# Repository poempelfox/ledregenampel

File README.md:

# LED-Regen-Ampel

## Intro

This is a small project that contains hardware design and
firmware for a small traffic-light-style display that shows
whether you can leave the house without getting wet. As it
utilizes regenampel.de to get the prediction, this is pretty
much useless outside of germany, which is why the rest of
the description is in german.

Haupt-Ziel dieses Projekts war es, mal eine Platine mit
richtig vielen LEDs drauf zu designen, um sie dann von einem
guenstigen Chinesischen Prototypenfertiger (JLCPCB) anfertigen
zu lassen.
Da ich ein Fan der [Regenampel](https://regenampel.de)
bin, kam die Idee auf, eine aus ganz vielen LEDs bestehende
Regenampel zu konstruieren, in einer Groesse die man bequem
neben die Wohnungstuer oder auch die Tuer des [ZAM](https://zam.haus)
haengen kann.

## Hardware Beschreibung Grob-Uebersicht

* ca. 21 x 7,5 cm grosse Platine
* Rot / Gelb / Gruen bestehend aus je 51 in konzentrischen Kreisen
  angeordneten LEDs (keine superhellen, generische in 0805 Gehaeuse),
  Durchmesser 5 cm.
* kleines OLED-Display unter der Ampel, um den Zusatztext den die
  Regenampel in manchen Situationen liefert (Beispiel: "Noch 20 Minuten
  starker Niederschlag") anzeigen zu koennen.
* Ein WaveShare ESP32-C3-Zero dient als zentrale Steuerung. Er wird
  auf die Rueckseite geloetet.
* Der ESP32-C3 steuert die LEDs ueber je einen MOSFET pro Farbe
  mit einem dedizierten I/O-Pin pro Farbe. Die Helligkeit kann dabei
  fuer jede Farbe einzeln ueber PWM mit 4096 Stufen geregelt werden.
  Das OLED wird ueber I2C angesprochen.
* momentaner Status: Hardware wurde geliefert und funktioniert zumindest
  teilweise.

## Hardware-Beschreibung Detail

Die Platine wurde in KiCad entworfen.
Die KiCad-Dateien finden sich im Unterverzeichnis [kicad/](kicad/).

Um die Platine nachbauen zu lassen, braucht man moeglicherweise
nichtmal KiCad zu oeffnen: Denn im Unterverzeichnis
[kicad/ledregenampel/jlcpcb/production_files/](kicad/ledregenampel/jlcpcb/production_files/)
finden sich die drei Dateien, die JLCPCB benoetigt um die Platine
zu fertigen: Das gerber-.zip, die BOM (Bill Of Materials), und das
CPL (Component PLacement). Verwendet wurde das, was im Juli 2024
dort auf Lager war. Solltet ihr zu einem spaeteren Zeitpunkt versuchen
das auch fertigen zu lassen, koennte es natuerlich sein dass Teile
nicht auf Lager sind und ersetzt werden muessen. Anders formuliert: YMMV.

Neben der gefertigten Platine sind nur zwei zusaetzliche Teile
notwendig:

* WaveShare ESP32-C3-Zero. Ein Microcontroller mit castellated mounting
  holes, so dass man ihn ohne Gefummel mit Buchsen- und Stiftleisten
  einfach auf die Rueckseite der Platine loeten kann. Der C3 ist zum
  Zeitpunkt dieses Projekts einer der kleinsten (und billigsten)
  Microcontroller die Espressif anbietet, fuer die ihm hier zugedachten
  Aufgaben aber immer noch deutlich ueberdimensioniert. Auf der
  Waveshare-Platine befindet sich u.a. eine USB-C-Buchse und ein
  Spannungsregler (Linearregler :-/) fuer die 3.3V.
* [Ein von TinyTronics bezogenes 2.08 inch OLED-Display mit 256x64 Pixeln](https://www.tinytronics.nl/en/displays/oled/2.08-inch-oled-display-256*64-pixels-white-i2c). Ich hatte
  ernsthafte Probleme, ein meinen Anforderungen nach "nicht winzig, I2C,
  extra-wide, 3.3V" entsprechendes Display zu finden, das war eines der
  wenigen passenden Angebote. Es handelt sich um ein Display
  des zumindest mir voellig unbekannten Herstellers "ZHONGJINGYUAN"
  mit einem SHT1122 Controller. Das Display wird ueber I2C
  angesprochen. Es wird auf die Vorderseite der LED-Regenampel-
  Platine geloetet.

Die USB-C-Buchse auf dem ESP32-Board ist der normale Weg, um
das Projekt mit Strom zu versorgen. USB-Power und "5V" Schiene
auf der Platine sind dabei einfach durchverbunden, d.h. es darf
falls auf andere Weise 5V eingespeist werden KEINESFALLS
gleichzeitig USB-C verbunden werden. Es ist ausserdem zu
beachten, dass der erwartete Stromverbrauch einer einzigen
Ampelfarbe bei 100% Helligkeit um 1A liegt. Es empfiehlt sich
also nicht, mehrere Ampelfarben gleichzeitig mit hoher
Helligkeit leuchten zu lassen.

Uebrigens sind 100% Helligkeit generell nicht der intendierte
Betriebsmodus. Mal abgesehen von dem geringfuegigen Problem,
dass das vermutlich den Betrachter der Ampel blind machen
wuerde, ist auch die dabei entstehende Abwaerme enorm -
die Platine wuerde wahrscheinlich recht schnell ueberhitzen.
"Normal" ist PWM mit unter 20% duty cycle...

## Hardware - known bugs

* Der ESP32-C3 wurde bei ersten Vorabtests alleine unangenehm
  heiss. Das ist laut "Internet" normal, und laut Specs darf
  der Chip auch bis zu 105 Grad. Nach dem aufloeten der Waveshare-
  Platine auf die grosse Platine scheint jedoch die
  Waerme sehr gut an die grosse Platine abgegeben zu werden,
  es ist kein nennenswerter Waermeherd mehr feststellbar.
* Die Loecher fuer das I2C-Display sind etwas arg klein geraten.
  Es passt gerade noch so, hat aber merklichen Widerstand beim
  einstecken der Display-Pins, und ist unschoen zu loeten.
  Dieser Fehler wurde im KiCad-.pcb-File bereits behoben.

## Firmware

* basiert auf der foxesptemp-Firmware.
* hat ein Admin-Webinterface, ueber das der angezeigte Ort (bzw. Weg)
  und die Helligkeit der Ampelfarben eingestellt werden kann.
* Hinweis: Der C3 wird anders programmiert als die meisten
  ESPs, es gibt naemlich keinen USB-seriell-Adapter auf der
  winzigen Platine. Stattdessen muss man: USB mit dem Rechner
  verbinden, dann den "Boot"-Knopf gedrueckt halten, dann
  kurz "Reset" druecken, dann kann man nach ein paar
  Sekunden "Boot" wieder loslassen. Dadurch geht der Chip
  in den Programmiermodus, der Bootloader emuliert einen
  USB-Seriell-Adapter, und man kann ihn wie gewohnt
  ueber idf.py flashen. Auch den Reset am Ende des Flashens
  muss man allerdings manuell machen, wieder ueber
  Knopfdruck. Gluecklicherweise muss man dieses komplexe
  Procedere nur ein mal zur Erstbefuellung durchfuehren:
  Die ledregenampel-firmware unterstuetzt Online-Firmware-
  Update ueber ihr Webinterface...

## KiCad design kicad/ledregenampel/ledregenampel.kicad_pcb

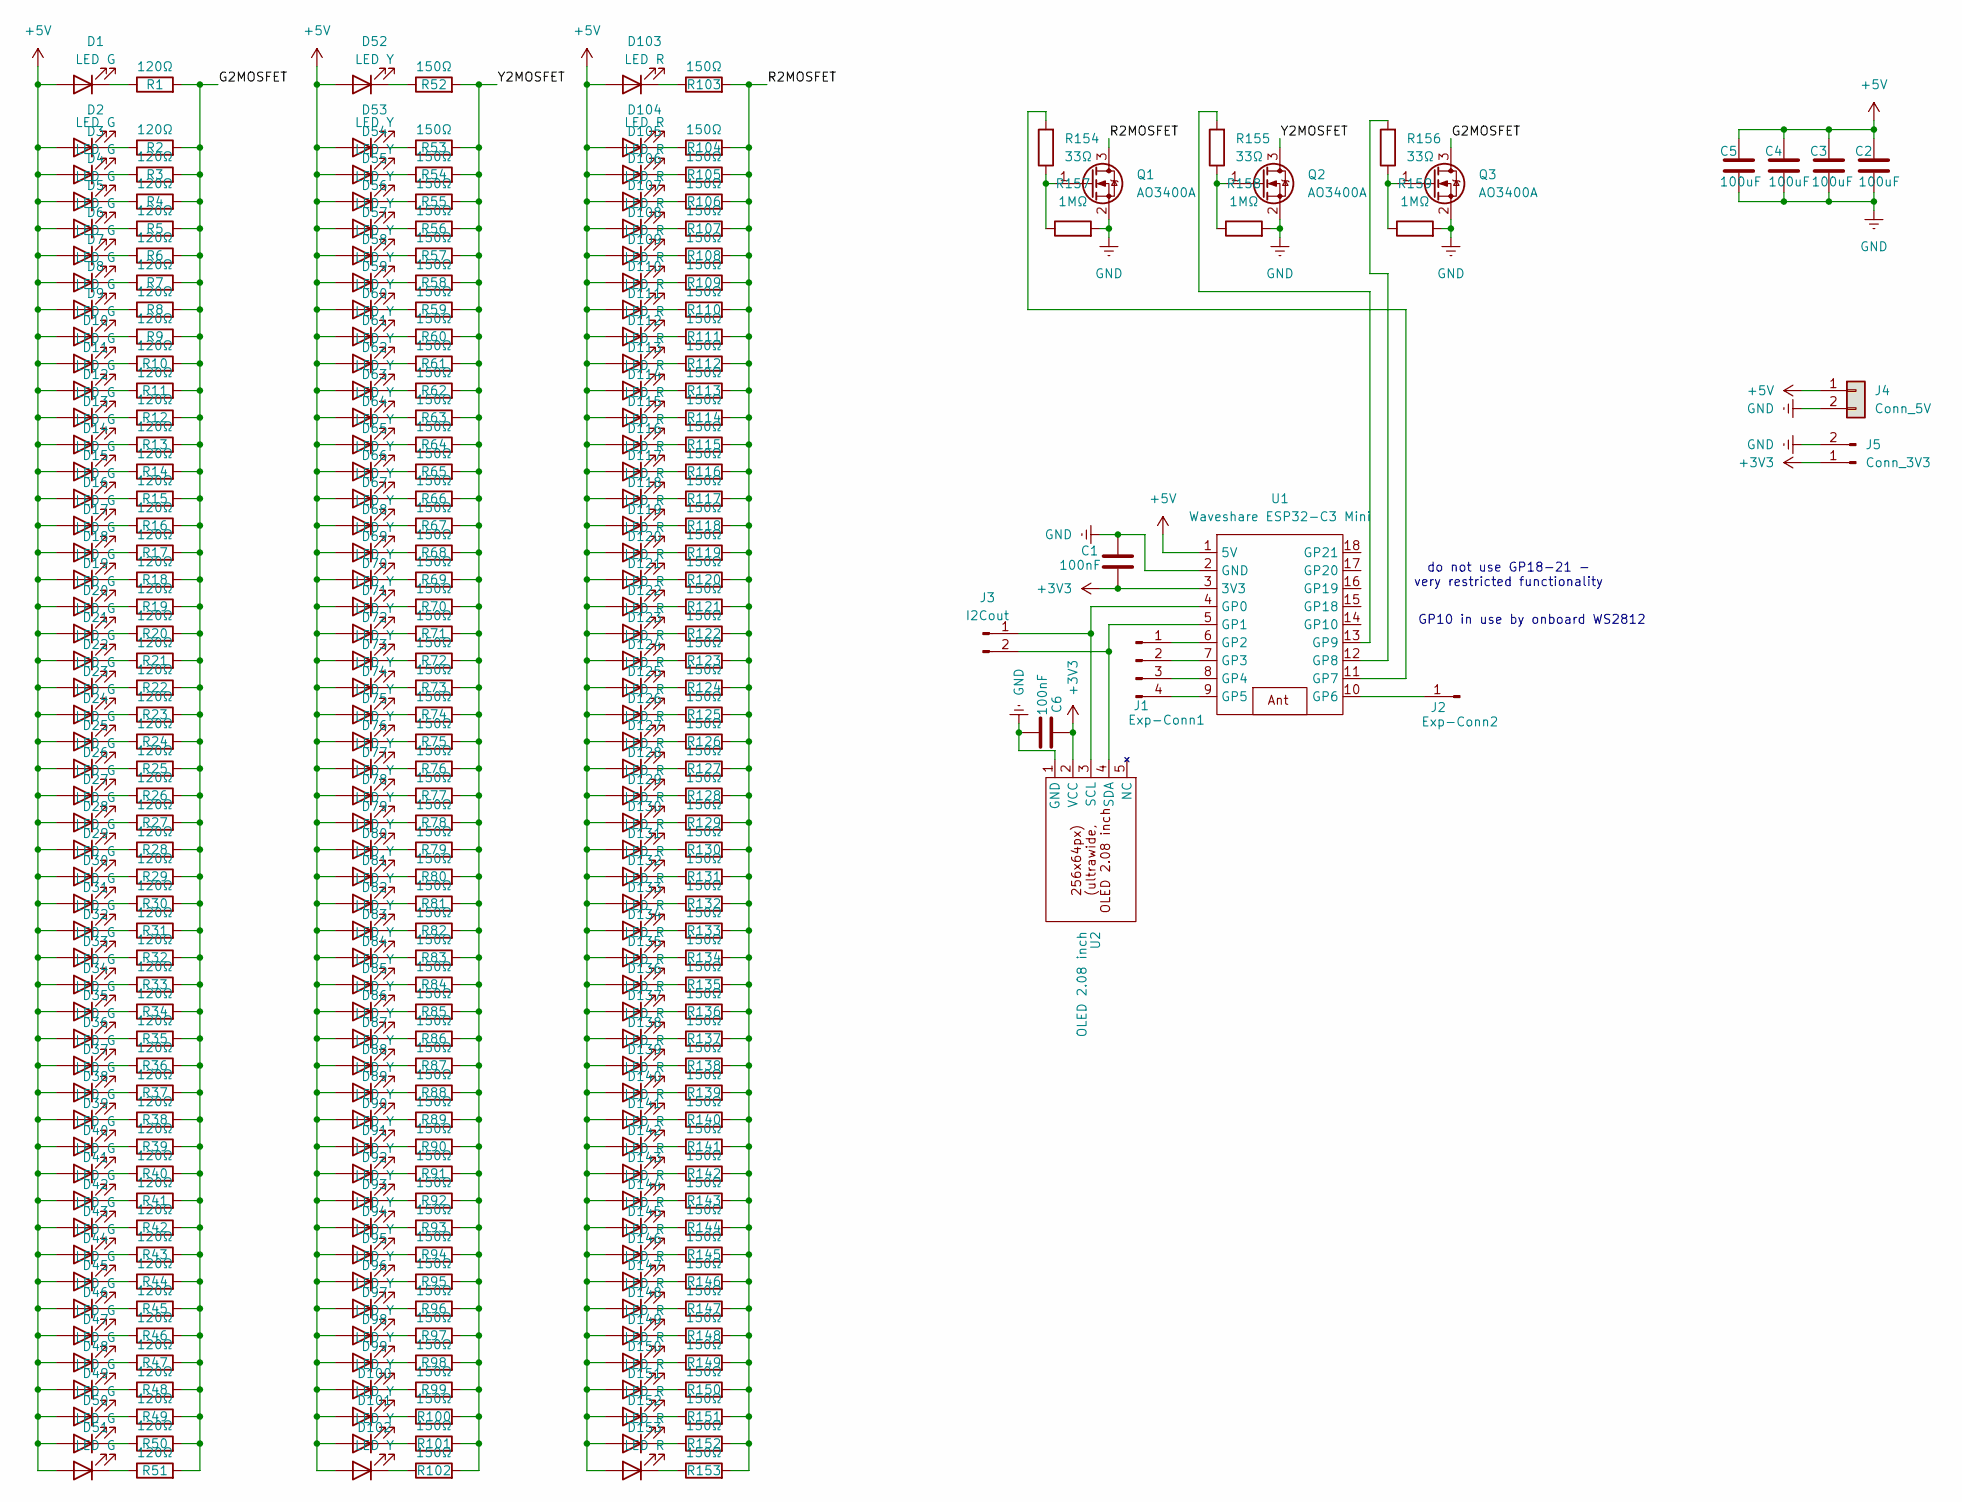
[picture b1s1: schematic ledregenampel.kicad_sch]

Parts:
C1, C6: 100nF; C_0402_1005Metric
C2, C3, C4, C5: 100uF; C_1206_3216Metric
D1, D2, D3, D4, D5, D6, D7, D8, D9, D10, D11, D12, D13, D14, D15, D16, D17, D18, D19, D20, D21, D22, D23, D24, D25, D26, D27, D28, D29, D30, D31, D32, D33, D34, D35, D36, D37, D38, D39, D40, D41, D42, D43, D44, D45, D46, D47, D48, D49, D50, D51: LED G; LED_0805_2012Metric
D52, D53, D54, D55, D56, D57, D58, D59, D60, D61, D62, D63, D64, D65, D66, D67, D68, D69, D70, D71, D72, D73, D74, D75, D76, D77, D78, D79, D80, D81, D82, D83, D84, D85, D86, D87, D88, D89, D90, D91, D92, D93, D94, D95, D96, D97, D98, D99, D100, D101, D102: LED Y; LED_0805_2012Metric
D103, D104, D105, D106, D107, D108, D109, D110, D111, D112, D113, D114, D115, D116, D117, D118, D119, D120, D121, D122, D123, D124, D125, D126, D127, D128, D129, D130, D131, D132, D133, D134, D135, D136, D137, D138, D139, D140, D141, D142, D143, D144, D145, D146, D147, D148, D149, D150, D151, D152, D153: LED R; LED_0805_2012Metric
J1: Exp-Conn1; PinHeader_1x04_P2.54mm_Vertical
J2: Exp-Conn2; PinHeader_1x01_P2.54mm_Vertical
J3: I2Cout; PinHeader_1x02_P2.54mm_Vertical
J4: Conn_5V; PinHeader_1x02_P2.54mm_Vertical
J5: Conn_3V3; PinHeader_1x02_P2.54mm_Vertical
Q1, Q2, Q3: AO3400A; SOT-23
R1, R2, R3, R4, R5, R6, R7, R8, R9, R10, R11, R12, R13, R14, R15, R16, R17, R18, R19, R20, R21, R22, R23, R24, R25, R26, R27, R28, R29, R30, R31, R32, R33, R34, R35, R36, R37, R38, R39, R40, R41, R42, R43, R44, R45, R46, R47, R48, R49, R50, R51: 120Ω; R_0402_modsilkscreen
R52, R53, R54, R55, R56, R57, R58, R59, R60, R61, R62, R63, R64, R65, R66, R67, R68, R69, R70, R71, R72, R73, R74, R75, R76, R77, R78, R79, R80, R81, R82, R83, R84, R85, R86, R87, R88, R89, R90, R91, R92, R93, R94, R95, R96, R97, R98, R99, R100, R101, R102, R103, R104, R105, R106, R107, R108, R109, R110, R111, R112, R113, R114, R115, R116, R117, R118, R119, R120, R121, R122, R123, R124, R125, R126, R127, R128, R129, R130, R131, R132, R133, R134, R135, R136, R137, R138, R139, R140, R141, R142, R143, R144, R145, R146, R147, R148, R149, R150, R151, R152, R153: 150Ω; R_0402_modsilkscreen
R154, R155, R156: 33Ω; R_0402_modsilkscreen
R157, R158, R159: 1MΩ; R_0402_modsilkscreen
U1: Waveshare ESP32-C3 Mini; Waveshare_ESP32-C3_Mini
U2: OLED 2.08 inch; OLED-2.08-inch

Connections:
+3V3: C1.1, C6.2, J5.1, U1.3 (3V3), U2.2 (VCC)
+5V: C2.1, C3.1, C4.1, C5.1, D1.2 (A), D2.2 (A), D3.2 (A), D4.2 (A), D5.2 (A), D6.2 (A), D7.2 (A), D8.2 (A), D9.2 (A), D10.2 (A), D11.2 (A), D12.2 (A), D13.2 (A), D14.2 (A), D15.2 (A), D16.2 (A), D17.2 (A), D18.2 (A), D19.2 (A), D20.2 (A), D21.2 (A), D22.2 (A), D23.2 (A), D24.2 (A), D25.2 (A), D26.2 (A), D27.2 (A), D28.2 (A), D29.2 (A), D30.2 (A), D31.2 (A), D32.2 (A), D33.2 (A), D34.2 (A), D35.2 (A), D36.2 (A), D37.2 (A), D38.2 (A), D39.2 (A), D40.2 (A), D41.2 (A), D42.2 (A), D43.2 (A), D44.2 (A), D45.2 (A), D46.2 (A), D47.2 (A), D48.2 (A), D49.2 (A), D50.2 (A), D51.2 (A), D52.2 (A), D53.2 (A), D54.2 (A), D55.2 (A), D56.2 (A), D57.2 (A), D58.2 (A), D59.2 (A), D60.2 (A), D61.2 (A), D62.2 (A), D63.2 (A), D64.2 (A), D65.2 (A), D66.2 (A), D67.2 (A), D68.2 (A), D69.2 (A), D70.2 (A), D71.2 (A), D72.2 (A), D73.2 (A), D74.2 (A), D75.2 (A), D76.2 (A), D77.2 (A), D78.2 (A), D79.2 (A), D80.2 (A), D81.2 (A), D82.2 (A), D83.2 (A), D84.2 (A), D85.2 (A), D86.2 (A), D87.2 (A), D88.2 (A), D89.2 (A), D90.2 (A), D91.2 (A), D92.2 (A), D93.2 (A), D94.2 (A), D95.2 (A), D96.2 (A), D97.2 (A), D98.2 (A), D99.2 (A), D100.2 (A), D101.2 (A), D102.2 (A), D103.2 (A), D104.2 (A), D105.2 (A), D106.2 (A), D107.2 (A), D108.2 (A), D109.2 (A), D110.2 (A), D111.2 (A), D112.2 (A), D113.2 (A), D114.2 (A), D115.2 (A), D116.2 (A), D117.2 (A), D118.2 (A), D119.2 (A), D120.2 (A), D121.2 (A), D122.2 (A), D123.2 (A), D124.2 (A), D125.2 (A), D126.2 (A), D127.2 (A), D128.2 (A), D129.2 (A), D130.2 (A), D131.2 (A), D132.2 (A), D133.2 (A), D134.2 (A), D135.2 (A), D136.2 (A), D137.2 (A), D138.2 (A), D139.2 (A), D140.2 (A), D141.2 (A), D142.2 (A), D143.2 (A), D144.2 (A), D145.2 (A), D146.2 (A), D147.2 (A), D148.2 (A), D149.2 (A), D150.2 (A), D151.2 (A), D152.2 (A), D153.2 (A), J4.1, U1.1 (5V)
/G2MOSFET: Q3.3 (D), R1.2, R2.2, R3.2, R4.2, R5.2, R6.2, R7.2, R8.2, R9.2, R10.2, R11.2, R12.2, R13.2, R14.2, R15.2, R16.2, R17.2, R18.2, R19.2, R20.2, R21.2, R22.2, R23.2, R24.2, R25.2, R26.2, R27.2, R28.2, R29.2, R30.2, R31.2, R32.2, R33.2, R34.2, R35.2, R36.2, R37.2, R38.2, R39.2, R40.2, R41.2, R42.2, R43.2, R44.2, R45.2, R46.2, R47.2, R48.2, R49.2, R50.2, R51.2
/R2MOSFET: Q1.3 (D), R103.2, R104.2, R105.2, R106.2, R107.2, R108.2, R109.2, R110.2, R111.2, R112.2, R113.2, R114.2, R115.2, R116.2, R117.2, R118.2, R119.2, R120.2, R121.2, R122.2, R123.2, R124.2, R125.2, R126.2, R127.2, R128.2, R129.2, R130.2, R131.2, R132.2, R133.2, R134.2, R135.2, R136.2, R137.2, R138.2, R139.2, R140.2, R141.2, R142.2, R143.2, R144.2, R145.2, R146.2, R147.2, R148.2, R149.2, R150.2, R151.2, R152.2, R153.2
/Y2MOSFET: Q2.3 (D), R52.2, R53.2, R54.2, R55.2, R56.2, R57.2, R58.2, R59.2, R60.2, R61.2, R62.2, R63.2, R64.2, R65.2, R66.2, R67.2, R68.2, R69.2, R70.2, R71.2, R72.2, R73.2, R74.2, R75.2, R76.2, R77.2, R78.2, R79.2, R80.2, R81.2, R82.2, R83.2, R84.2, R85.2, R86.2, R87.2, R88.2, R89.2, R90.2, R91.2, R92.2, R93.2, R94.2, R95.2, R96.2, R97.2, R98.2, R99.2, R100.2, R101.2, R102.2
GND: C1.2, C2.2, C3.2, C4.2, C5.2, C6.1, J4.2, J5.2, Q1.2 (S), Q2.2 (S), Q3.2 (S), R157.2, R158.2, R159.2, U1.2 (GND), U2.1 (GND)
unnamed: D1.1 (K), R1.1
unnamed: D2.1 (K), R2.1
unnamed: D3.1 (K), R3.1
unnamed: D4.1 (K), R4.1
unnamed: D5.1 (K), R5.1
unnamed: D6.1 (K), R6.1
unnamed: D7.1 (K), R7.1
unnamed: D8.1 (K), R8.1
unnamed: D9.1 (K), R9.1
unnamed: D10.1 (K), R10.1
unnamed: D11.1 (K), R11.1
unnamed: D12.1 (K), R12.1
unnamed: D13.1 (K), R13.1
unnamed: D14.1 (K), R14.1
unnamed: D15.1 (K), R15.1
unnamed: D16.1 (K), R16.1
unnamed: D17.1 (K), R17.1
unnamed: D18.1 (K), R18.1
unnamed: D19.1 (K), R19.1
unnamed: D20.1 (K), R20.1
unnamed: D21.1 (K), R21.1
unnamed: D22.1 (K), R22.1
unnamed: D23.1 (K), R23.1
unnamed: D24.1 (K), R24.1
unnamed: D25.1 (K), R25.1
unnamed: D26.1 (K), R26.1
unnamed: D27.1 (K), R27.1
unnamed: D28.1 (K), R28.1
unnamed: D29.1 (K), R29.1
unnamed: D30.1 (K), R30.1
unnamed: D31.1 (K), R31.1
unnamed: D32.1 (K), R32.1
unnamed: D33.1 (K), R33.1
unnamed: D34.1 (K), R34.1
unnamed: D35.1 (K), R35.1
unnamed: D36.1 (K), R36.1
unnamed: D37.1 (K), R37.1
unnamed: D38.1 (K), R38.1
unnamed: D39.1 (K), R39.1
unnamed: D40.1 (K), R40.1
unnamed: D41.1 (K), R41.1
unnamed: D42.1 (K), R42.1
unnamed: D43.1 (K), R43.1
unnamed: D44.1 (K), R44.1
unnamed: D45.1 (K), R45.1
unnamed: D46.1 (K), R46.1
unnamed: D47.1 (K), R47.1
unnamed: D48.1 (K), R48.1
unnamed: D49.1 (K), R49.1
unnamed: D50.1 (K), R50.1
unnamed: D51.1 (K), R51.1
unnamed: D52.1 (K), R52.1
unnamed: D53.1 (K), R53.1
unnamed: D54.1 (K), R54.1
unnamed: D55.1 (K), R55.1
unnamed: D56.1 (K), R56.1
unnamed: D57.1 (K), R57.1
unnamed: D58.1 (K), R58.1
unnamed: D59.1 (K), R59.1
unnamed: D60.1 (K), R60.1
unnamed: D61.1 (K), R61.1
unnamed: D62.1 (K), R62.1
unnamed: D63.1 (K), R63.1
unnamed: D64.1 (K), R64.1
unnamed: D65.1 (K), R65.1
unnamed: D66.1 (K), R66.1
unnamed: D67.1 (K), R67.1
unnamed: D68.1 (K), R68.1
unnamed: D69.1 (K), R69.1
unnamed: D70.1 (K), R70.1
unnamed: D71.1 (K), R71.1
unnamed: D72.1 (K), R72.1
unnamed: D73.1 (K), R73.1
unnamed: D74.1 (K), R74.1
unnamed: D75.1 (K), R75.1
unnamed: D76.1 (K), R76.1
unnamed: D77.1 (K), R77.1
unnamed: D78.1 (K), R78.1
unnamed: D79.1 (K), R79.1
unnamed: D80.1 (K), R80.1
unnamed: D81.1 (K), R81.1
unnamed: D82.1 (K), R82.1
unnamed: D83.1 (K), R83.1
unnamed: D84.1 (K), R84.1
unnamed: D85.1 (K), R85.1
unnamed: D86.1 (K), R86.1
unnamed: D87.1 (K), R87.1
unnamed: D88.1 (K), R88.1
unnamed: D89.1 (K), R89.1
unnamed: D90.1 (K), R90.1
unnamed: D91.1 (K), R91.1
unnamed: D92.1 (K), R92.1
unnamed: D93.1 (K), R93.1
unnamed: D94.1 (K), R94.1
unnamed: D95.1 (K), R95.1
unnamed: D96.1 (K), R96.1
unnamed: D97.1 (K), R97.1
unnamed: D98.1 (K), R98.1
unnamed: D99.1 (K), R99.1
unnamed: D100.1 (K), R100.1
unnamed: D101.1 (K), R101.1
unnamed: D102.1 (K), R102.1
unnamed: D103.1 (K), R103.1
unnamed: D104.1 (K), R104.1
unnamed: D105.1 (K), R105.1
unnamed: D106.1 (K), R106.1
unnamed: D107.1 (K), R107.1
unnamed: D108.1 (K), R108.1
unnamed: D109.1 (K), R109.1
unnamed: D110.1 (K), R110.1
unnamed: D111.1 (K), R111.1
unnamed: D112.1 (K), R112.1
unnamed: D113.1 (K), R113.1
unnamed: D114.1 (K), R114.1
unnamed: D115.1 (K), R115.1
unnamed: D116.1 (K), R116.1
unnamed: D117.1 (K), R117.1
unnamed: D118.1 (K), R118.1
unnamed: D119.1 (K), R119.1
unnamed: D120.1 (K), R120.1
unnamed: D121.1 (K), R121.1
unnamed: D122.1 (K), R122.1
unnamed: D123.1 (K), R123.1
unnamed: D124.1 (K), R124.1
unnamed: D125.1 (K), R125.1
unnamed: D126.1 (K), R126.1
unnamed: D127.1 (K), R127.1
unnamed: D128.1 (K), R128.1
unnamed: D129.1 (K), R129.1
unnamed: D130.1 (K), R130.1
unnamed: D131.1 (K), R131.1
unnamed: D132.1 (K), R132.1
unnamed: D133.1 (K), R133.1
unnamed: D134.1 (K), R134.1
unnamed: D135.1 (K), R135.1
unnamed: D136.1 (K), R136.1
unnamed: D137.1 (K), R137.1
unnamed: D138.1 (K), R138.1
unnamed: D139.1 (K), R139.1
unnamed: D140.1 (K), R140.1
unnamed: D141.1 (K), R141.1
unnamed: D142.1 (K), R142.1
unnamed: D143.1 (K), R143.1
unnamed: D144.1 (K), R144.1
unnamed: D145.1 (K), R145.1
unnamed: D146.1 (K), R146.1
unnamed: D147.1 (K), R147.1
unnamed: D148.1 (K), R148.1
unnamed: D149.1 (K), R149.1
unnamed: D150.1 (K), R150.1
unnamed: D151.1 (K), R151.1
unnamed: D152.1 (K), R152.1
unnamed: D153.1 (K), R153.1
unnamed: J1.1, U1.6 (GP2)
unnamed: J1.2, U1.7 (GP3)
unnamed: J1.3, U1.8 (GP4)
unnamed: J1.4, U1.9 (GP5)
unnamed: J2.1, U1.10 (GP6)
unnamed: J3.1, U1.4 (GP0), U2.3 (SCL)
unnamed: J3.2, U1.5 (GP1), U2.4 (SDA)
unnamed: Q1.1 (G), R154.1, R157.1
unnamed: Q2.1 (G), R155.1, R158.1
unnamed: Q3.1 (G), R156.1, R159.1
unnamed: R154.2, U1.11 (GP7)
unnamed: R156.2, U1.12 (GP8)
unnamed: R155.2, U1.13 (GP9)

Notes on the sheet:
do not use GP18-21 - very restricted functionality
GP10 in use by onboard WS2812

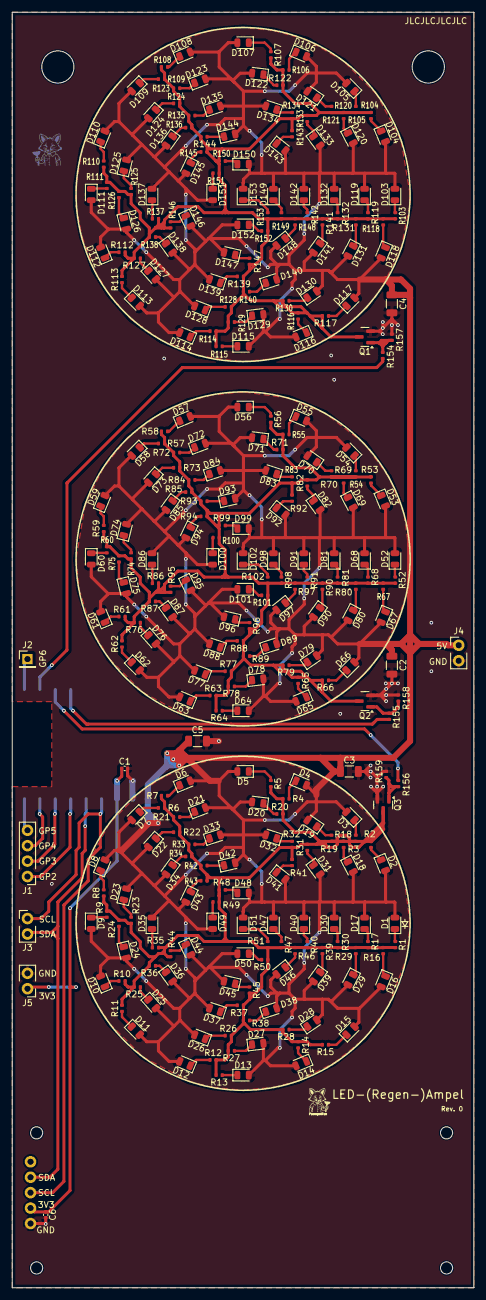
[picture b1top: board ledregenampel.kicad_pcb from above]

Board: 2 copper layers, 76.0 x 210.0 mm, 330 parts (1 on the bottom side), 172 nets.

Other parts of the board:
mnthole1, mnthole2: MountingHole_5.3mm_M5

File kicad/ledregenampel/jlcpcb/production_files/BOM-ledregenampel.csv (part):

Comment,Designator,Footprint,LCSC
C1,100nF,C_0402_1005Metric,C1525,26786529,0,0
C2,100uF,C_1206_3216Metric,C15008,1087743,0,0
C3,100uF,C_1206_3216Metric,C15008,1087743,0,0
C4,100uF,C_1206_3216Metric,C15008,1087743,0,0
C5,100uF,C_1206_3216Metric,C15008,1087743,0,0
C6,100nF,C_0402_1005Metric,C1525,26786529,0,0
D1,LED G,LED_0805_2012Metric,C688883,15123,0,0
D10,LED G,LED_0805_2012Metric,C688883,15123,0,0
D100,LED Y,LED_0805_2012Metric,C779458,3875,0,0
D101,LED Y,LED_0805_2012Metric,C779458,3875,0,0
D102,LED Y,LED_0805_2012Metric,C779458,3875,0,0
D103,LED R,LED_0805_2012Metric,C688884,23736,0,0
D104,LED R,LED_0805_2012Metric,C688884,23736,0,0
D105,LED R,LED_0805_2012Metric,C688884,23736,0,0
D106,LED R,LED_0805_2012Metric,C688884,23736,0,0
D107,LED R,LED_0805_2012Metric,C688884,23736,0,0
D108,LED R,LED_0805_2012Metric,C688884,23736,0,0
D109,LED R,LED_0805_2012Metric,C688884,23736,0,0
D11,LED G,LED_0805_2012Metric,C688883,15123,0,0
D110,LED R,LED_0805_2012Metric,C688884,23736,0,0
D111,LED R,LED_0805_2012Metric,C688884,23736,0,0
D112,LED R,LED_0805_2012Metric,C688884,23736,0,0
D113,LED R,LED_0805_2012Metric,C688884,23736,0,0
D114,LED R,LED_0805_2012Metric,C688884,23736,0,0
D115,LED R,LED_0805_2012Metric,C688884,23736,0,0
D116,LED R,LED_0805_2012Metric,C688884,23736,0,0
D117,LED R,LED_0805_2012Metric,C688884,23736,0,0
D118,LED R,LED_0805_2012Metric,C688884,23736,0,0
D119,LED R,LED_0805_2012Metric,C688884,23736,0,0
D12,LED G,LED_0805_2012Metric,C688883,15123,0,0
D120,LED R,LED_0805_2012Metric,C688884,23736,0,0
D121,LED R,LED_0805_2012Metric,C688884,23736,0,0
D122,LED R,LED_0805_2012Metric,C688884,23736,0,0
D123,LED R,LED_0805_2012Metric,C688884,23736,0,0
D124,LED R,LED_0805_2012Metric,C688884,23736,0,0
D125,LED R,LED_0805_2012Metric,C688884,23736,0,0
D126,LED R,LED_0805_2012Metric,C688884,23736,0,0
D127,LED R,LED_0805_2012Metric,C688884,23736,0,0
D128,LED R,LED_0805_2012Metric,C688884,23736,0,0
D129,LED R,LED_0805_2012Metric,C688884,23736,0,0
D13,LED G,LED_0805_2012Metric,C688883,15123,0,0
D130,LED R,LED_0805_2012Metric,C688884,23736,0,0
D131,LED R,LED_0805_2012Metric,C688884,23736,0,0
D132,LED R,LED_0805_2012Metric,C688884,23736,0,0
D133,LED R,LED_0805_2012Metric,C688884,23736,0,0
D134,LED R,LED_0805_2012Metric,C688884,23736,0,0
D135,LED R,LED_0805_2012Metric,C688884,23736,0,0
D136,LED R,LED_0805_2012Metric,C688884,23736,0,0
D137,LED R,LED_0805_2012Metric,C688884,23736,0,0
D138,LED R,LED_0805_2012Metric,C688884,23736,0,0
D139,LED R,LED_0805_2012Metric,C688884,23736,0,0
D14,LED G,LED_0805_2012Metric,C688883,15123,0,0
D140,LED R,LED_0805_2012Metric,C688884,23736,0,0
D141,LED R,LED_0805_2012Metric,C688884,23736,0,0
D142,LED R,LED_0805_2012Metric,C688884,23736,0,0
D143,LED R,LED_0805_2012Metric,C688884,23736,0,0
D144,LED R,LED_0805_2012Metric,C688884,23736,0,0
D145,LED R,LED_0805_2012Metric,C688884,23736,0,0
D146,LED R,LED_0805_2012Metric,C688884,23736,0,0
D147,LED R,LED_0805_2012Metric,C688884,23736,0,0
D148,LED R,LED_0805_2012Metric,C688884,23736,0,0
D149,LED R,LED_0805_2012Metric,C688884,23736,0,0
D15,LED G,LED_0805_2012Metric,C688883,15123,0,0
D150,LED R,LED_0805_2012Metric,C688884,23736,0,0
D151,LED R,LED_0805_2012Metric,C688884,23736,0,0
D152,LED R,LED_0805_2012Metric,C688884,23736,0,0
D153,LED R,LED_0805_2012Metric,C688884,23736,0,0
D16,LED G,LED_0805_2012Metric,C688883,15123,0,0
D17,LED G,LED_0805_2012Metric,C688883,15123,0,0
D18,LED G,LED_0805_2012Metric,C688883,15123,0,0
D19,LED G,LED_0805_2012Metric,C688883,15123,0,0
D2,LED G,LED_0805_2012Metric,C688883,15123,0,0
D20,LED G,LED_0805_2012Metric,C688883,15123,0,0
D21,LED G,LED_0805_2012Metric,C688883,15123,0,0
D22,LED G,LED_0805_2012Metric,C688883,15123,0,0
D23,LED G,LED_0805_2012Metric,C688883,15123,0,0
D24,LED G,LED_0805_2012Metric,C688883,15123,0,0
D25,LED G,LED_0805_2012Metric,C688883,15123,0,0
D26,LED G,LED_0805_2012Metric,C688883,15123,0,0
D27,LED G,LED_0805_2012Metric,C688883,15123,0,0
D28,LED G,LED_0805_2012Metric,C688883,15123,0,0
D29,LED G,LED_0805_2012Metric,C688883,15123,0,0
D3,LED G,LED_0805_2012Metric,C688883,15123,0,0
D30,LED G,LED_0805_2012Metric,C688883,15123,0,0
D31,LED G,LED_0805_2012Metric,C688883,15123,0,0
D32,LED G,LED_0805_2012Metric,C688883,15123,0,0
D33,LED G,LED_0805_2012Metric,C688883,15123,0,0
D34,LED G,LED_0805_2012Metric,C688883,15123,0,0
D35,LED G,LED_0805_2012Metric,C688883,15123,0,0
D36,LED G,LED_0805_2012Metric,C688883,15123,0,0
D37,LED G,LED_0805_2012Metric,C688883,15123,0,0
D38,LED G,LED_0805_2012Metric,C688883,15123,0,0
D39,LED G,LED_0805_2012Metric,C688883,15123,0,0
D4,LED G,LED_0805_2012Metric,C688883,15123,0,0
D40,LED G,LED_0805_2012Metric,C688883,15123,0,0
D41,LED G,LED_0805_2012Metric,C688883,15123,0,0
D42,LED G,LED_0805_2012Metric,C688883,15123,0,0
D43,LED G,LED_0805_2012Metric,C688883,15123,0,0
D44,LED G,LED_0805_2012Metric,C688883,15123,0,0
D45,LED G,LED_0805_2012Metric,C688883,15123,0,0
D46,LED G,LED_0805_2012Metric,C688883,15123,0,0
D47,LED G,LED_0805_2012Metric,C688883,15123,0,0
D48,LED G,LED_0805_2012Metric,C688883,15123,0,0
D49,LED G,LED_0805_2012Metric,C688883,15123,0,0
D5,LED G,LED_0805_2012Metric,C688883,15123,0,0
D50,LED G,LED_0805_2012Metric,C688883,15123,0,0
D51,LED G,LED_0805_2012Metric,C688883,15123,0,0
D52,LED Y,LED_0805_2012Metric,C779458,3875,0,0
D53,LED Y,LED_0805_2012Metric,C779458,3875,0,0
D54,LED Y,LED_0805_2012Metric,C779458,3875,0,0
D55,LED Y,LED_0805_2012Metric,C779458,3875,0,0
D56,LED Y,LED_0805_2012Metric,C779458,3875,0,0
D57,LED Y,LED_0805_2012Metric,C779458,3875,0,0
D58,LED Y,LED_0805_2012Metric,C779458,3875,0,0
D59,LED Y,LED_0805_2012Metric,C779458,3875,0,0
D6,LED G,LED_0805_2012Metric,C688883,15123,0,0
D60,LED Y,LED_0805_2012Metric,C779458,3875,0,0
D61,LED Y,LED_0805_2012Metric,C779458,3875,0,0
D62,LED Y,LED_0805_2012Metric,C779458,3875,0,0
D63,LED Y,LED_0805_2012Metric,C779458,3875,0,0
D64,LED Y,LED_0805_2012Metric,C779458,3875,0,0
D65,LED Y,LED_0805_2012Metric,C779458,3875,0,0
D66,LED Y,LED_0805_2012Metric,C779458,3875,0,0
D67,LED Y,LED_0805_2012Metric,C779458,3875,0,0
D68,LED Y,LED_0805_2012Metric,C779458,3875,0,0
D69,LED Y,LED_0805_2012Metric,C779458,3875,0,0
D7,LED G,LED_0805_2012Metric,C688883,15123,0,0
D70,LED Y,LED_0805_2012Metric,C779458,3875,0,0
D71,LED Y,LED_0805_2012Metric,C779458,3875,0,0
D72,LED Y,LED_0805_2012Metric,C779458,3875,0,0
D73,LED Y,LED_0805_2012Metric,C779458,3875,0,0
D74,LED Y,LED_0805_2012Metric,C779458,3875,0,0
D75,LED Y,LED_0805_2012Metric,C779458,3875,0,0
D76,LED Y,LED_0805_2012Metric,C779458,3875,0,0
D77,LED Y,LED_0805_2012Metric,C779458,3875,0,0
D78,LED Y,LED_0805_2012Metric,C779458,3875,0,0
D79,LED Y,LED_0805_2012Metric,C779458,3875,0,0
D8,LED G,LED_0805_2012Metric,C688883,15123,0,0
D80,LED Y,LED_0805_2012Metric,C779458,3875,0,0
D81,LED Y,LED_0805_2012Metric,C779458,3875,0,0
D82,LED Y,LED_0805_2012Metric,C779458,3875,0,0
D83,LED Y,LED_0805_2012Metric,C779458,3875,0,0
D84,LED Y,LED_0805_2012Metric,C779458,3875,0,0
D85,LED Y,LED_0805_2012Metric,C779458,3875,0,0
D86,LED Y,LED_0805_2012Metric,C779458,3875,0,0
D87,LED Y,LED_0805_2012Metric,C779458,3875,0,0
D88,LED Y,LED_0805_2012Metric,C779458,3875,0,0
D89,LED Y,LED_0805_2012Metric,C779458,3875,0,0
D9,LED G,LED_0805_2012Metric,C688883,15123,0,0
D90,LED Y,LED_0805_2012Metric,C779458,3875,0,0
D91,LED Y,LED_0805_2012Metric,C779458,3875,0,0
D92,LED Y,LED_0805_2012Metric,C779458,3875,0,0
D93,LED Y,LED_0805_2012Metric,C779458,3875,0,0
D94,LED Y,LED_0805_2012Metric,C779458,3875,0,0
D95,LED Y,LED_0805_2012Metric,C779458,3875,0,0
D96,LED Y,LED_0805_2012Metric,C779458,3875,0,0
D97,LED Y,LED_0805_2012Metric,C779458,3875,0,0
D98,LED Y,LED_0805_2012Metric,C779458,3875,0,0
D99,LED Y,LED_0805_2012Metric,C779458,3875,0,0
Q1,AO3400A,SOT-23,C20917,628525,0,0
Q2,AO3400A,SOT-23,C20917,628525,0,0
Q3,AO3400A,SOT-23,C20917,628525,0,0
R1,120Ω,R_0402_modsilkscreen,C25079,547006,0,0
R10,120Ω,R_0402_modsilkscreen,C25079,547006,0,0
R100,150Ω,R_0402_modsilkscreen,C25143,39000,0,0
R101,150Ω,R_0402_modsilkscreen,C25143,39000,0,0
R102,150Ω,R_0402_modsilkscreen,C25143,39000,0,0
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
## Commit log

2024-06-30 first of three lights (green) is done.
2024-07-06 lets call this RC1
2024-07-08 mostly more labelling
2024-07-08 add jlcpcb production files
2024-07-12 final rev. 0 as ordered from JLCPCB.
2024-07-12 adding mini-readme.
2024-07-14 initial checkin for firmware: mostly an empty hull.
2024-07-14 we're not a foxtemp
2024-07-14 clock down CPU and enable some other powermanagement, but unfortunately the ESP32-C3 still gets very hot - most power is probably used by the WiFi.
2024-07-17 we need to increase the header length limit of the internal webserver, it's way too low by default.
2024-07-17 support for controlling the leds, including being able to set the PWM brightness per channel through the admin-webinterface.
2024-07-17 small status update
2024-07-18 expose the leds_setbrightness function and clarify comments.
2024-07-22 big progress - we now query the regenampel-augmented-api, and we show the correct light color.
2024-07-27 Make the holes for connecting the display bigger. the display pins barely got through, they were no fun to solder. Lets avoid that problem in a possible future revision.
2024-07-27 moar documentation
2024-07-27 implement support for our OLED display. doesn't display anything useful yet, but works.
2024-07-27 show messages on the webpage and on the OLED. OLED-messages are cut off because we're currently doing just two lines with a very large font, we'll be changing that.
2024-07-28 switch our font system to use structures compatible with adafruit_gfx. the main reason for that is that this permits us to reuse their fontconverter with minor modifications, so I don't have to reinv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
2024-07-28 add our modified version of the adafruit_gfx fontconverter. We mainly hacked in the ability to use select additional characters like umlauts - but unfortunately we did so in a very messy way that we 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
2024-07-28 implement splitting text into 3 lines for the OLED, implement properly displaying special chars like umlauts (at least for the few or embedded-font has), split display.[ch] from sh1122.[ch]
2024-08-01 add hint about programming the ESP32-C3
2024-08-01 try to update 10 seconds after booting up, and implement blinking yellow when no (current) data is available.
2024-08-01 add another special char: &szlig; (sharp small s)
2024-08-04 implement "test" mode for LED brightness settings (settings are applied instantly, but not save to flash).
2024-08-07 Add an automatically increasing build number to our version number this is implemented by a bash-script that updates version.txt automatically and is called on every build.
2024-09-14 flash all LEDs at very low brightness, and show firmware-version/IP on boot.
